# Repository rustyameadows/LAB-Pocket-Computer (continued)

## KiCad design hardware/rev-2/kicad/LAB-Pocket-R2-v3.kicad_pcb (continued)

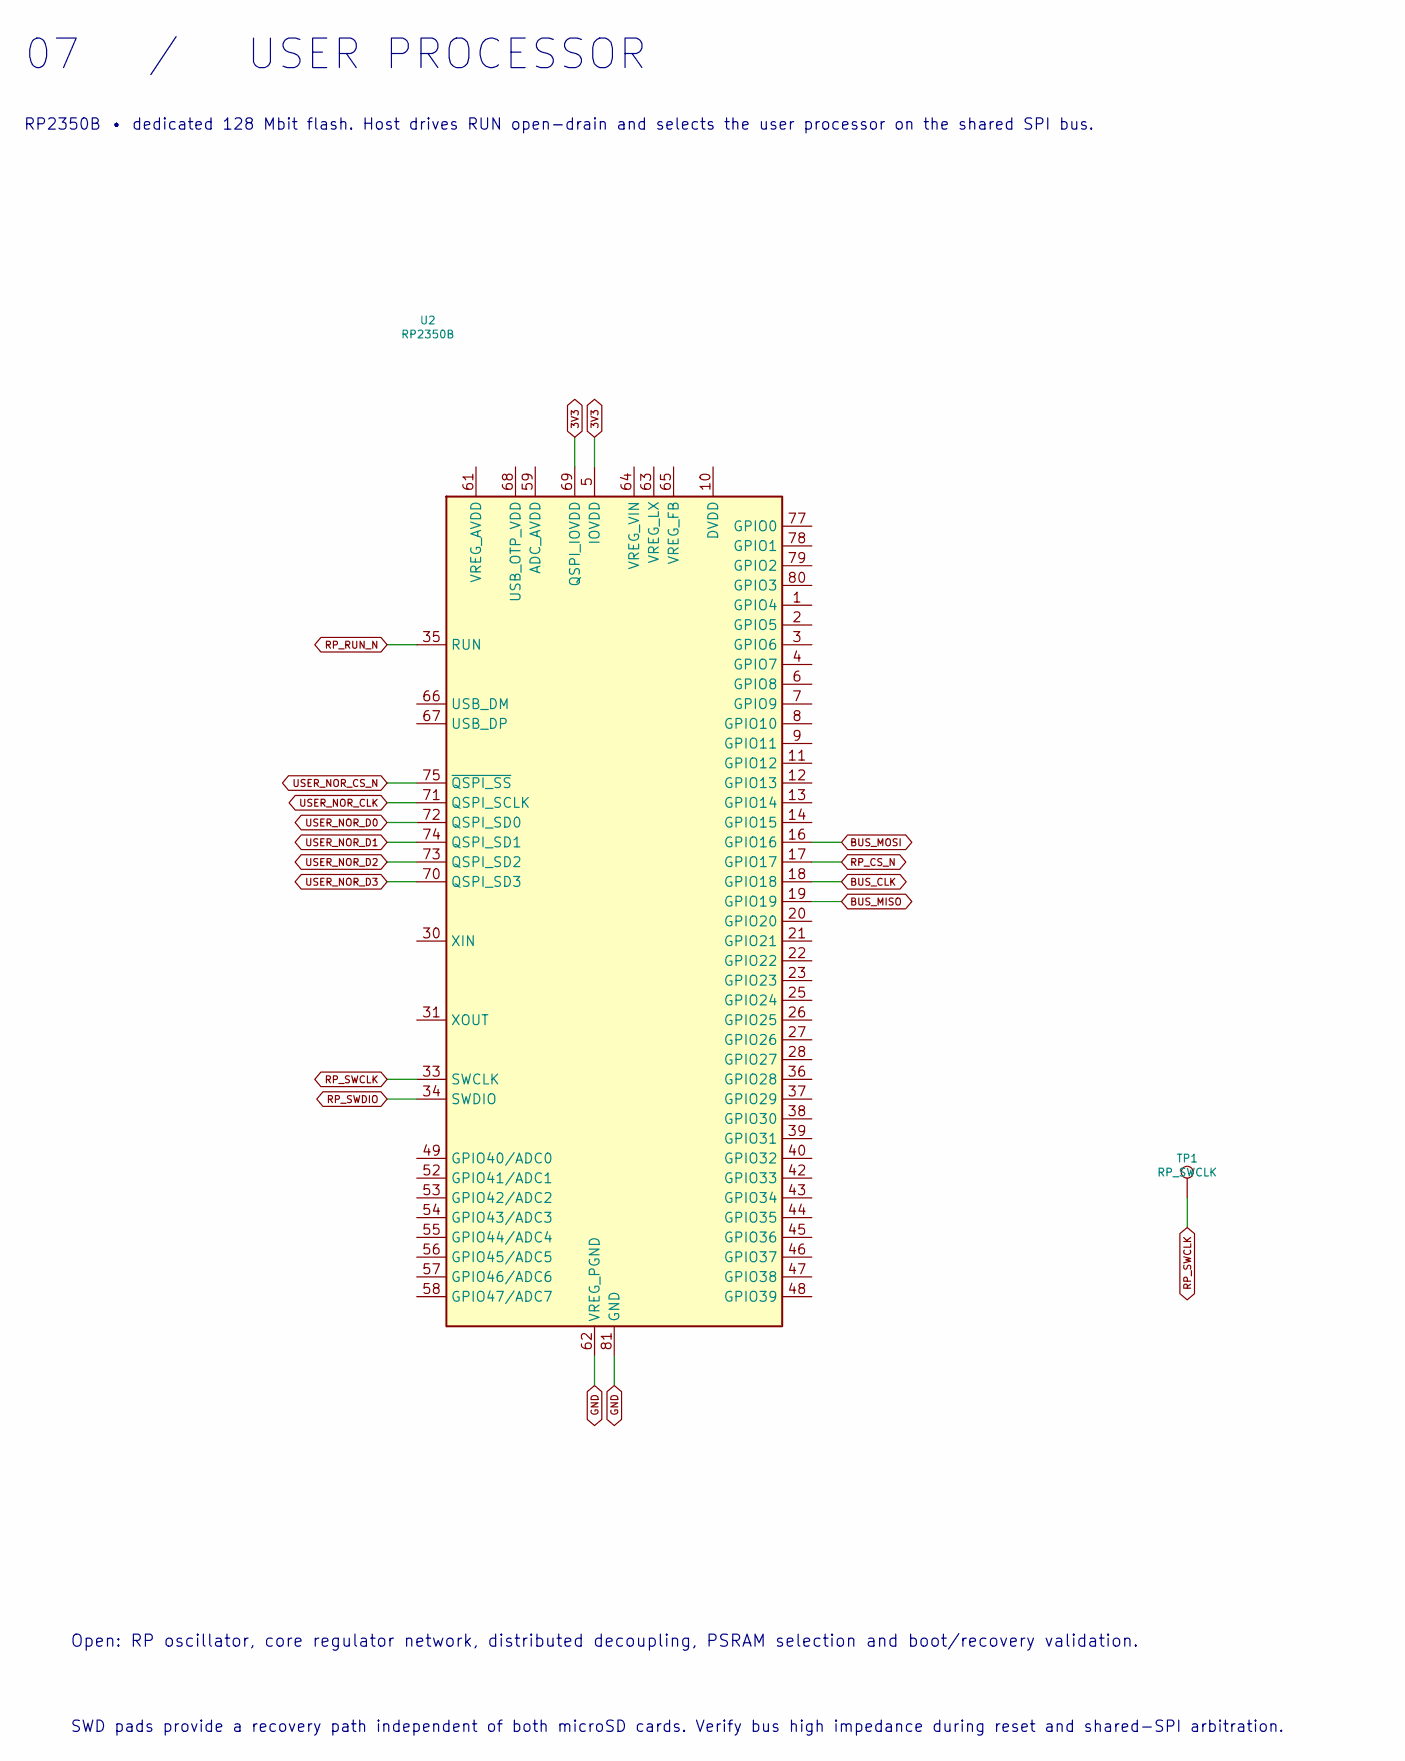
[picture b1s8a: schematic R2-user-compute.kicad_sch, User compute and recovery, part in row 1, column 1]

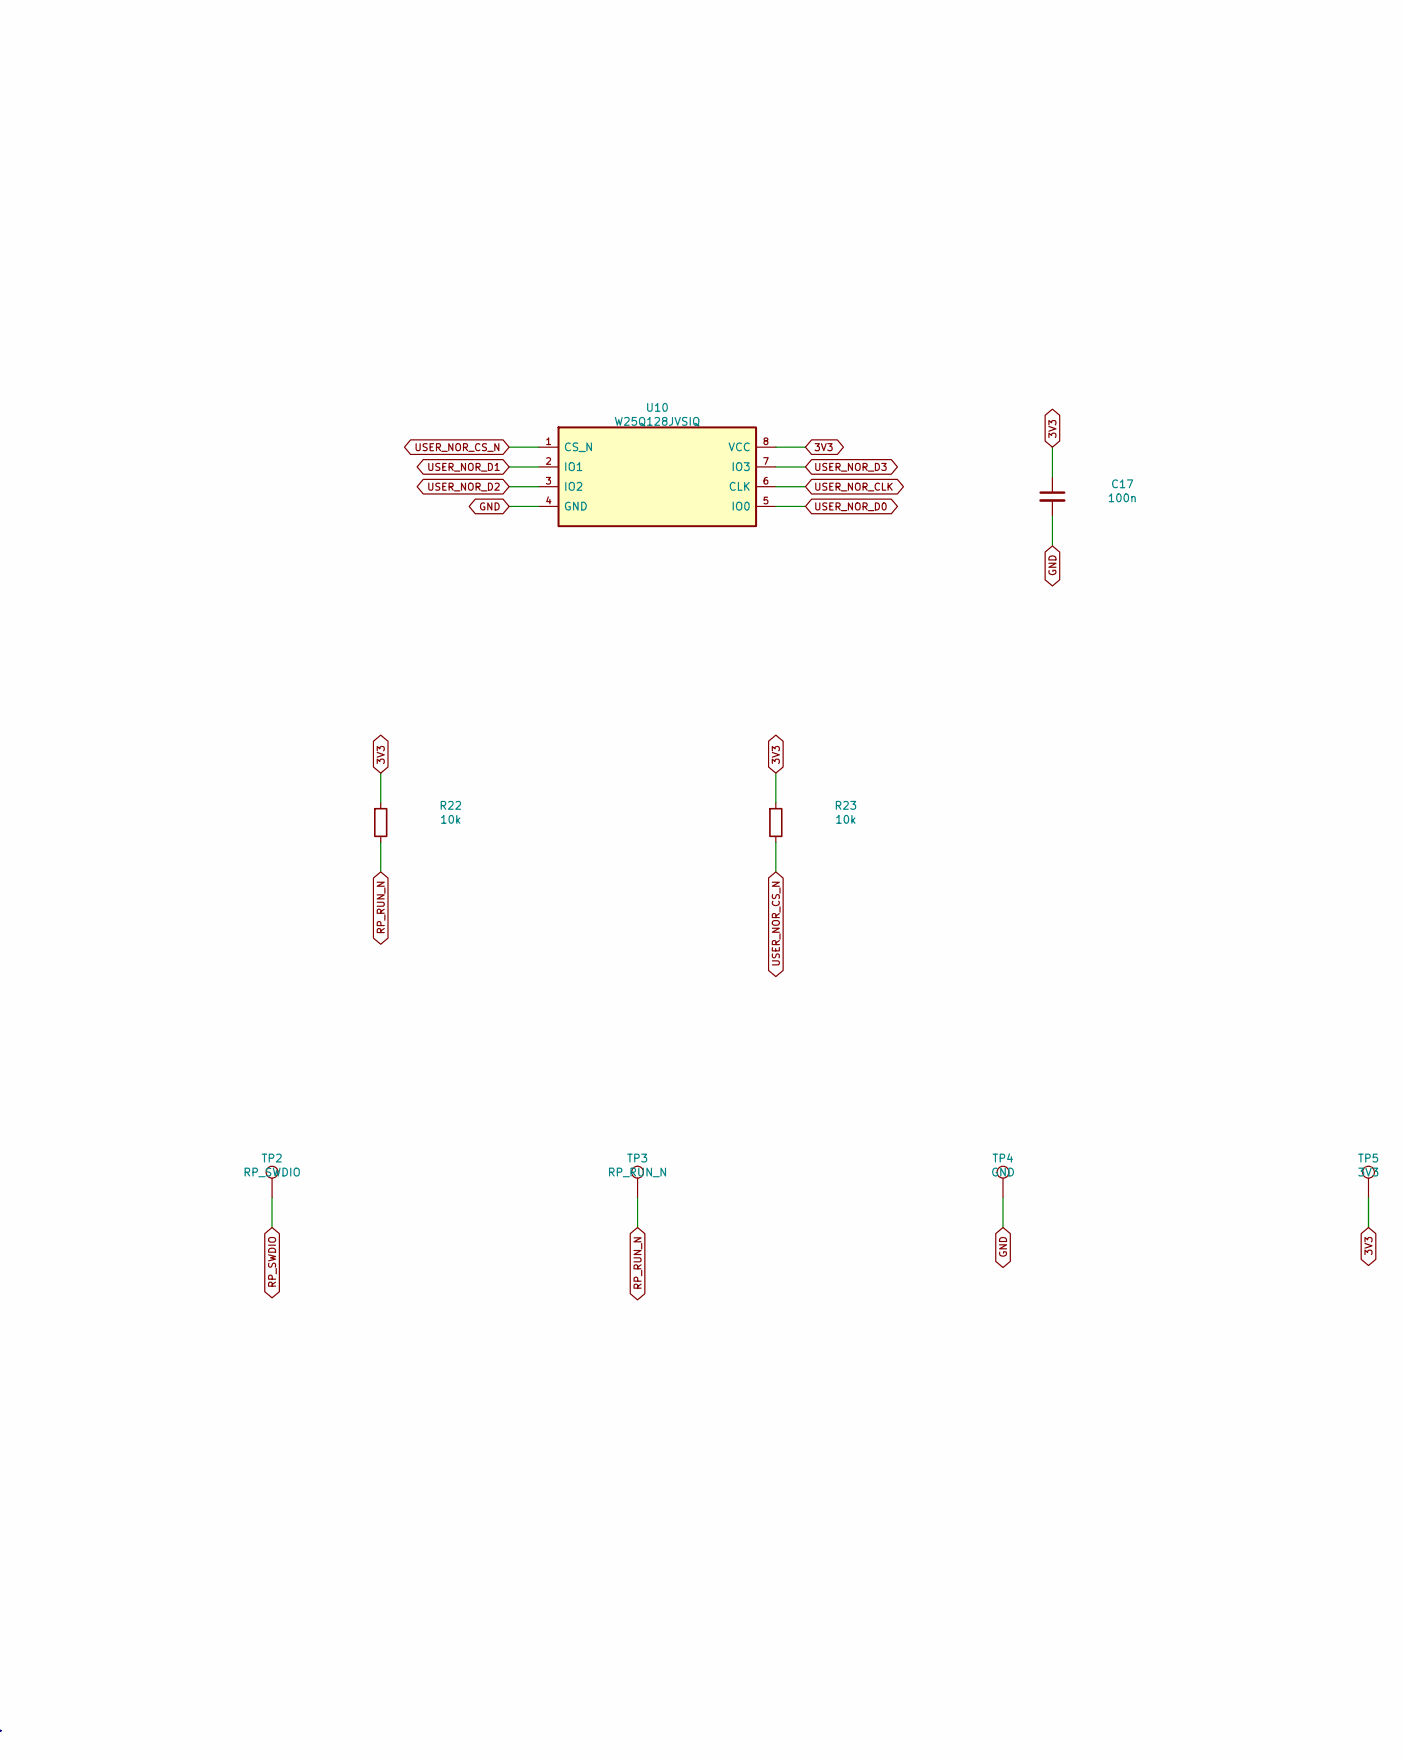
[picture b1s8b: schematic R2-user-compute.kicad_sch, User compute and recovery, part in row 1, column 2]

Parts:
C17: 100n; C_0603_1608Metric; MPN C0603C104K5RACTU
R22, R23: 10k; R_0603_1608Metric; MPN CRCW060310K0FKEA
TP1: RP_SWCLK; TestPoint_Pad_D1.0mm; MPN PCB feature
TP2: RP_SWDIO; TestPoint_Pad_D1.0mm; MPN PCB feature
TP3: RP_RUN_N; TestPoint_Pad_D1.0mm; MPN PCB feature
TP4: GND; TestPoint_Pad_D1.0mm; MPN PCB feature
TP5: 3V3; TestPoint_Pad_D1.0mm; MPN PCB feature
U2: RP2350B; QFN-80-1EP_10x10mm_P0.4mm_EP3.4x3.4mm; MPN RP2350B
U10: W25Q128JVSIQ; SOIC-8_5.3x5.3mm_P1.27mm; MPN W25Q128JVSIQ

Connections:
3V3: C17.1, R22.1, R23.1, TP5.1, U2.5 (IOVDD), U2.15 (IOVDD), U2.24 (IOVDD), U2.29 (IOVDD), U2.41 (IOVDD), U2.50 (IOVDD), U2.60 (IOVDD), U2.69 (QSPI_IOVDD), U2.76 (IOVDD), U10.8 (VCC); also elsewhere on the board
BUS_CLK: U2.18 (GPIO18); also elsewhere on the board
BUS_MISO: U2.19 (GPIO19); also elsewhere on the board
BUS_MOSI: U2.16 (GPIO16); also elsewhere on the board
GND: C17.2, TP4.1, U2.62 (VREG_PGND), U2.81 (GND), U10.4 (GND); also elsewhere on the board
unnamed: U2.10 (DVDD), U2.32 (DVDD), U2.51 (DVDD)
RP_CS_N: U2.17 (GPIO17); also elsewhere on the board
RP_RUN_N: R22.2, TP3.1, U2.35 (RUN); also elsewhere on the board
RP_SWCLK: TP1.1, U2.33 (SWCLK)
RP_SWDIO: TP2.1, U2.34 (SWDIO)
USER_NOR_CLK: U2.71 (QSPI_SCLK), U10.6 (CLK)
USER_NOR_CS_N: R23.2, U2.75 (~QSPI_SS), U10.1 (CS_N)
USER_NOR_D0: U2.72 (QSPI_SD0), U10.5 (IO0)
USER_NOR_D1: U2.74 (QSPI_SD1), U10.2 (IO1)
USER_NOR_D2: U2.73 (QSPI_SD2), U10.3 (IO2)
USER_NOR_D3: U2.70 (QSPI_SD3), U10.7 (IO3)

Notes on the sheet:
07 / USER PROCESSOR
RP2350B • dedicated 128 Mbit flash. Host drives RUN open-drain and selects the user processor on the shared SPI bus.
Open: RP oscillator, core regulator network, distributed decoupling, PSRAM selection and boot/recovery validation.
SWD pads provide a recovery path independent of both microSD cards. Verify bus high impedance during reset and shared-SPI arbitration.

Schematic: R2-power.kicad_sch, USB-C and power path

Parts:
BT1: LP735977JH; MPN LP735977JH+PCM+2 WIRES 70MM
C18: 1u; C_0603_1608Metric; MPN C0603C105K8PACTU
C19, C20: 4.7u; C_0805_2012Metric; MPN C0805C475K8PACTU
J1: USB4105-GF-A; USB_C_Receptacle_GCT_USB4105-xx-A_16P_TopMnt_Horizontal; MPN USB4105-GF-A
J6: JST PH • keyed harness; JST_PH_S3B-PH-SM4-TB_1x03-1MP_P2.00mm_Horizontal; MPN S3B-PH-SM4-TB
R24, R25: 5.1k; R_0603_1608Metric; MPN CRCW06035K10FKEA
R26: 2.2k; R_0603_1608Metric; MPN CRCW06032K20FKEA
R27: 3.0k; R_0603_1608Metric; MPN CRCW06033K00FKEA
U11: BQ24074RGTR; VQFN-16-1EP_3x3mm_P0.5mm_EP1.6x1.6mm; MPN BQ24074RGTR

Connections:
CC1: J1.A5 (CC1), R24.1
CC2: J1.B5 (CC2), R25.1
CHG_ISET: R26.1, U11.16 (ISET)
GND: BT1.2 (PACK_NEG), C18.2, C19.2, C20.2, J1.A1 (GND), J1.A12 (GND), J1.B1 (GND), J1.B12 (GND), J1.SH (SHIELD), J6.1, R24.2, R25.2, R26.2, R27.2, U11.5 (EN2), U11.6 (EN1), U11.8 (VSS), U11.17 (VSS); also elsewhere on the board
ILIM_SET: R27.1, U11.12 (ILIM)
PACK_POS: BT1.1 (PACK_POS), C20.1, J6.3, U11.2 (BAT), U11.3 (BAT)
PACK_TS: J6.2, U11.1 (TS)
USB_DM: J1.A7 (D-), J1.B7 (D-); also elsewhere on the board
USB_DP: J1.A6 (D+), J1.B6 (D+); also elsewhere on the board
VBUS: C18.1, J1.A4 (VBUS), J1.A9 (VBUS), J1.B4 (VBUS), J1.B9 (VBUS), U11.13 (IN)
VSYS: C19.1, U11.4 (~CE), U11.10 (OUT), U11.11 (OUT)

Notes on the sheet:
08 / USB / POWER PATH
BQ24074 single-cell power path. Charging is held disabled for the first electrical review.
EN1=EN2=0 selects USB100. CE tracks OUT to inhibit charging. Two-wire battery requires a qualified external thermistor. J6 pin 1 = GND, 2 = TS, 3 = BAT+.
Review cable current, inrush, ESD, ISET, ILIM, temperature range and thermal layout before enabling charge. VSYS is an unregulated system output.
Unimplemented: VSYS to 3V3 buck-boost, LCD/backlight supply, switched LED 5 V, MCU core rails and fuel gauge.

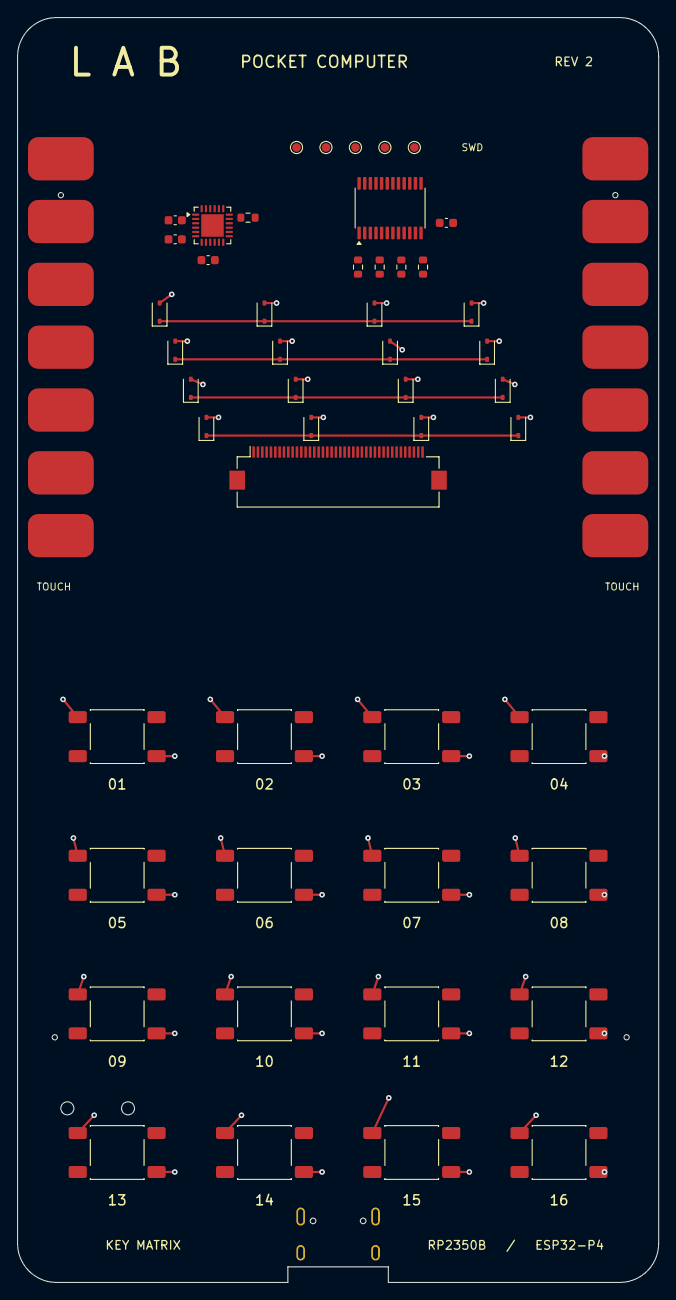
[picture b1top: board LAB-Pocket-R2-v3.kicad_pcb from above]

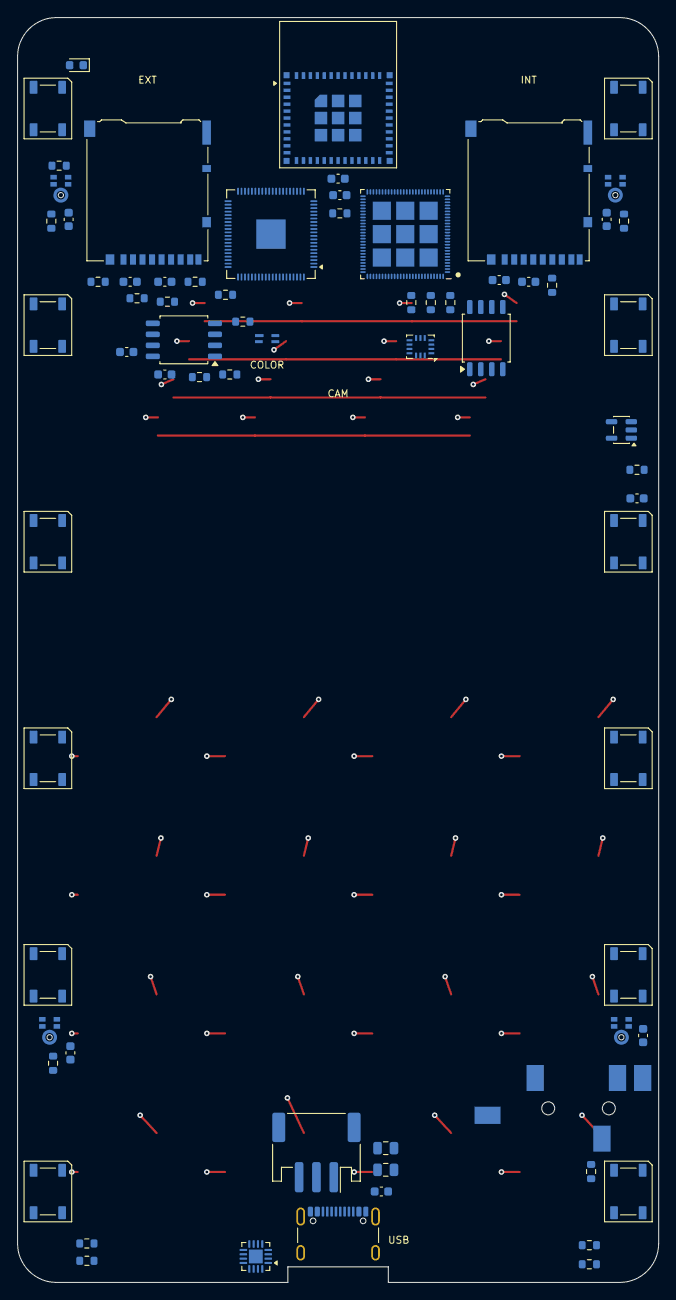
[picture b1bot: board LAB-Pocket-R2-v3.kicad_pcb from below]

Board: 4 copper layers, 74.0 x 146.0 mm, 133 parts (70 on the bottom side), 137 nets.
